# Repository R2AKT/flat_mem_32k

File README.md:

License addendum - https://github.com/R2AKT/flat_mem_32k/blob/main/Addendum.txt
# flat_mem_32k

32k flat (linear) memory board: 8k ROM + 8k EEPROM/RAM + 8k EEPROM/RAM + 8k RAM.
For Mega-80 (Mega-580) DIY 8-bit micro-computer - https://github.com/R2AKT/Mega-80.

ROM - 8k;
PROM - 8/16k;
RAM - 16/8k.

Status: not tested!

Плата плоской (линейной) памяти на 8к.
Для самодельной 8-битной микро-ЭВМ - https://github.com/R2AKT/Mega-80.

ПЗУ - 8кб;
ППЗУ - 8/16кб;
ОЗУ - 16/8кб.

Статус: не проверено!

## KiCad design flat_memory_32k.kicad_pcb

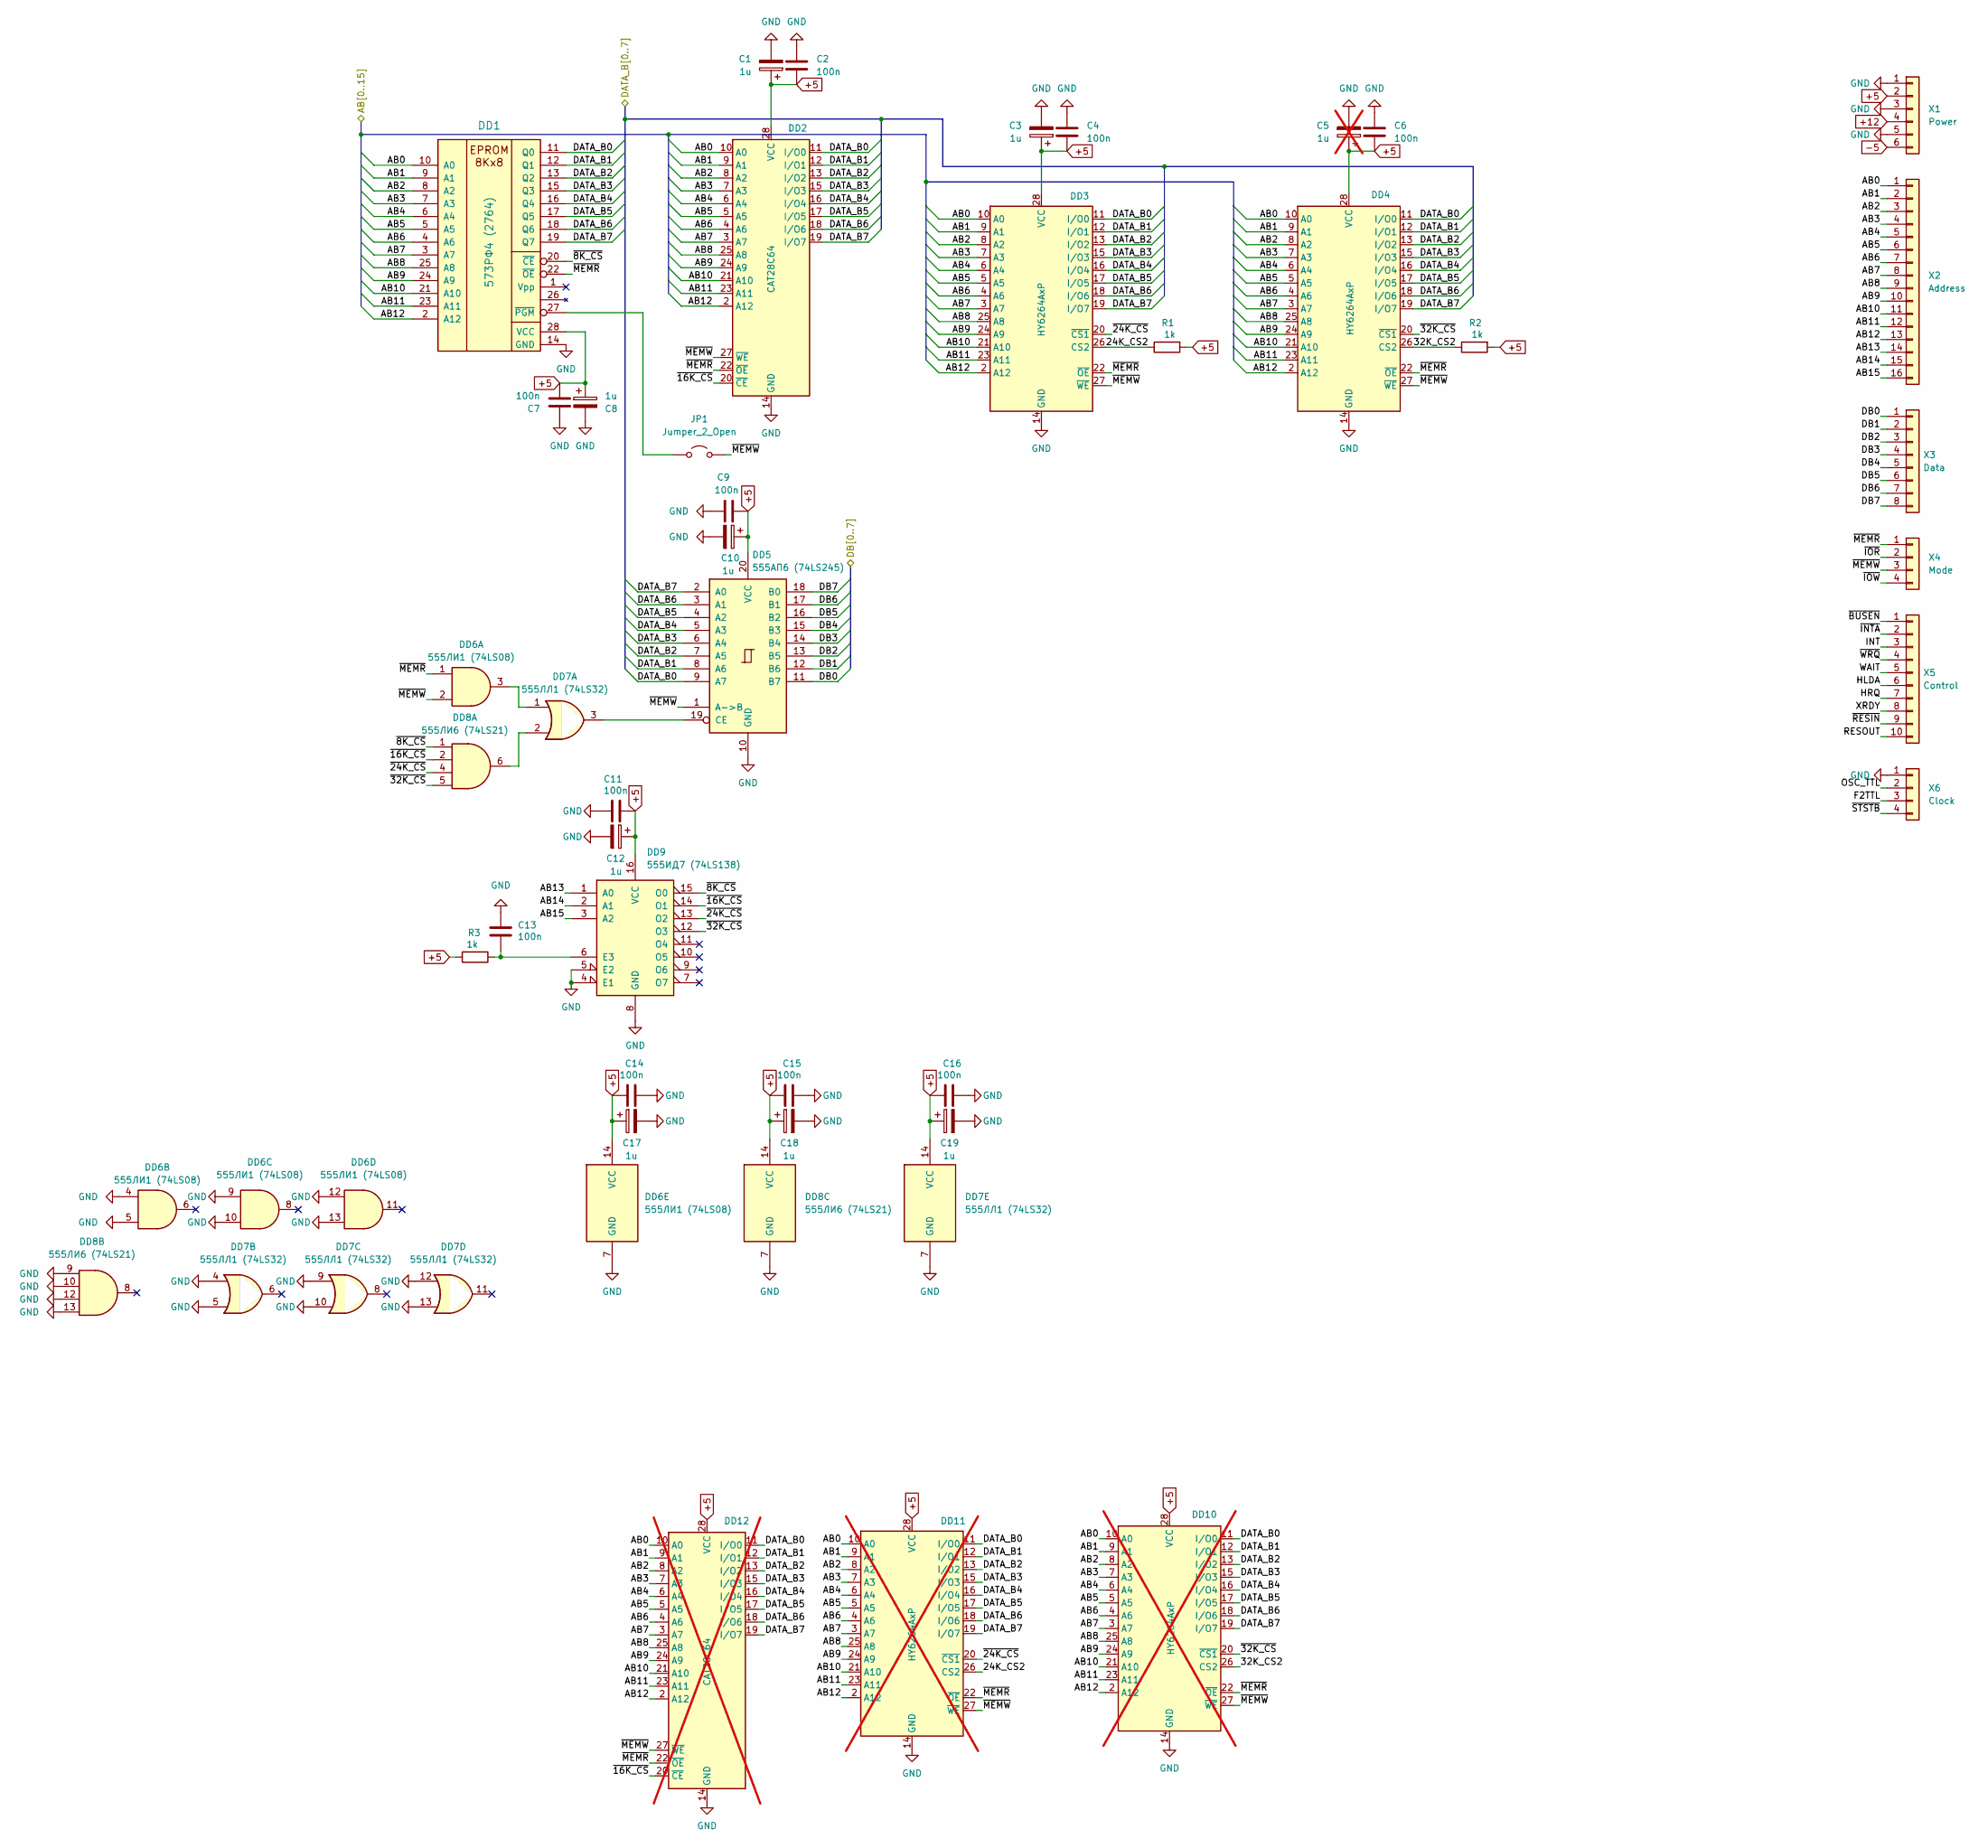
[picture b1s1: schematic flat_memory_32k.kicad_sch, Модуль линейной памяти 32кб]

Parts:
C1, C3, C8, C10, C12, C17, C18, C19: 1u; CP_EIA-3216-18_Kemet-A_Pad1.58x1.35mm_HandSolder
C2, C4, C6, C7, C9, C11, C13, C14, C15, C16: 100n; C_0805_2012Metric_Pad1.18x1.45mm_HandSolder
C5: 1u; CP_EIA-3216-18_Kemet-A_Pad1.58x1.35mm_HandSolder; not fitted
DD1: 573РФ4 (2764); DIP-28_W15.24mm_Socket_LongPads
DD2: CAT28C64; DIP-28_W15.24mm_Socket_LongPads
DD3, DD4: HY6264AxP; DIP-28_W15.24mm_Socket_LongPads
DD5: 555АП6 (74LS245); DIP-20_W7.62mm_Socket_LongPads
DD6: 555ЛИ1 (74LS08); DIP-14_W7.62mm_Socket_LongPads
DD7: 555ЛЛ1 (74LS32); DIP-14_W7.62mm_Socket_LongPads
DD8: 555ЛИ6 (74LS21); DIP-14_W7.62mm_Socket_LongPads
DD9: 555ИД7 (74LS138); DIP-16_W7.62mm_Socket_LongPads
DD10, DD11: HY6264AxP; DIP-28_W7.62mm_Socket_LongPads; not fitted
DD12: CAT28C64; DIP-28_W7.62mm_Socket_LongPads; not fitted
JP1: Jumper_2_Open; SolderJumper-2_P1.3mm_Open_RoundedPad1.0x1.5mm
R1, R2, R3: 1k; R_0805_2012Metric_Pad1.20x1.40mm_HandSolder
X1: Power; PinHeader_1x06_P2.54mm_Vertical
X2: Address; PinHeader_1x16_P2.54mm_Vertical
X3: Data; PinHeader_1x08_P2.54mm_Vertical
X4: Mode; PinHeader_1x04_P2.54mm_Vertical
X5: Control; PinHeader_1x10_P2.54mm_Vertical
X6: Clock; PinHeader_1x04_P2.54mm_Vertical

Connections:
+5: C1.1, C2.1, C3.1, C4.1, C5.1, C6.1, C7.1, C8.1, C9.1, C10.1, C11.1, C12.1, C14.1, C15.1, C16.1, C17.1, C18.1, C19.1, DD1.28 (VCC), DD2.28 (VCC), DD3.28 (VCC), DD4.28 (VCC), DD5.20 (VCC), DD6.14 (VCC), DD7.14 (VCC), DD8.14 (VCC), DD9.16 (VCC), DD10.28 (VCC), DD11.28 (VCC), DD12.28 (VCC), R1.2, R2.2, R3.2, X1.2
+12: X1.4
-5: X1.6
/24K_CS2: DD3.26 (CS2), DD11.26 (CS2), R1.1
/32K_CS2: DD4.26 (CS2), DD10.26 (CS2), R2.1
/AB0: DD1.10 (A0), DD2.10 (A0), DD3.10 (A0), DD4.10 (A0), DD10.10 (A0), DD11.10 (A0), DD12.10 (A0), X2.1
/AB1: DD1.9 (A1), DD2.9 (A1), DD3.9 (A1), DD4.9 (A1), DD10.9 (A1), DD11.9 (A1), DD12.9 (A1), X2.2
/AB2: DD1.8 (A2), DD2.8 (A2), DD3.8 (A2), DD4.8 (A2), DD10.8 (A2), DD11.8 (A2), DD12.8 (A2), X2.3
/AB3: DD1.7 (A3), DD2.7 (A3), DD3.7 (A3), DD4.7 (A3), DD10.7 (A3), DD11.7 (A3), DD12.7 (A3), X2.4
/AB4: DD1.6 (A4), DD2.6 (A4), DD3.6 (A4), DD4.6 (A4), DD10.6 (A4), DD11.6 (A4), DD12.6 (A4), X2.5
/AB5: DD1.5 (A5), DD2.5 (A5), DD3.5 (A5), DD4.5 (A5), DD10.5 (A5), DD11.5 (A5), DD12.5 (A5), X2.6
/AB6: DD1.4 (A6), DD2.4 (A6), DD3.4 (A6), DD4.4 (A6), DD10.4 (A6), DD11.4 (A6), DD12.4 (A6), X2.7
/AB7: DD1.3 (A7), DD2.3 (A7), DD3.3 (A7), DD4.3 (A7), DD10.3 (A7), DD11.3 (A7), DD12.3 (A7), X2.8
/AB8: DD1.25 (A8), DD2.25 (A8), DD3.25 (A8), DD4.25 (A8), DD10.25 (A8), DD11.25 (A8), DD12.25 (A8), X2.9
/AB9: DD1.24 (A9), DD2.24 (A9), DD3.24 (A9), DD4.24 (A9), DD10.24 (A9), DD11.24 (A9), DD12.24 (A9), X2.10
/AB10: DD1.21 (A10), DD2.21 (A10), DD3.21 (A10), DD4.21 (A10), DD10.21 (A10), DD11.21 (A10), DD12.21 (A10), X2.11
/AB11: DD1.23 (A11), DD2.23 (A11), DD3.23 (A11), DD4.23 (A11), DD10.23 (A11), DD11.23 (A11), DD12.23 (A11), X2.12
/AB12: DD1.2 (A12), DD2.2 (A12), DD3.2 (A12), DD4.2 (A12), DD10.2 (A12), DD11.2 (A12), DD12.2 (A12), X2.13
/AB13: DD9.1 (A0), X2.14
/AB14: DD9.2 (A1), X2.15
/AB15: DD9.3 (A2), X2.16
/DATA_B0: DD1.11 (Q0), DD2.11 (I/O0), DD3.11 (I/O0), DD4.11 (I/O0), DD5.9 (A7), DD10.11 (I/O0), DD11.11 (I/O0), DD12.11 (I/O0)
/DATA_B1: DD1.12 (Q1), DD2.12 (I/O1), DD3.12 (I/O1), DD4.12 (I/O1), DD5.8 (A6), DD10.12 (I/O1), DD11.12 (I/O1), DD12.12 (I/O1)
/DATA_B2: DD1.13 (Q2), DD2.13 (I/O2), DD3.13 (I/O2), DD4.13 (I/O2), DD5.7 (A5), DD10.13 (I/O2), DD11.13 (I/O2), DD12.13 (I/O2)
/DATA_B3: DD1.15 (Q3), DD2.15 (I/O3), DD3.15 (I/O3), DD4.15 (I/O3), DD5.6 (A4), DD10.15 (I/O3), DD11.15 (I/O3), DD12.15 (I/O3)
/DATA_B4: DD1.16 (Q4), DD2.16 (I/O4), DD3.16 (I/O4), DD4.16 (I/O4), DD5.5 (A3), DD10.16 (I/O4), DD11.16 (I/O4), DD12.16 (I/O4)
/DATA_B5: DD1.17 (Q5), DD2.17 (I/O5), DD3.17 (I/O5), DD4.17 (I/O5), DD5.4 (A2), DD10.17 (I/O5), DD11.17 (I/O5), DD12.17 (I/O5)
/DATA_B6: DD1.18 (Q6), DD2.18 (I/O6), DD3.18 (I/O6), DD4.18 (I/O6), DD5.3 (A1), DD10.18 (I/O6), DD11.18 (I/O6), DD12.18 (I/O6)
/DATA_B7: DD1.19 (Q7), DD2.19 (I/O7), DD3.19 (I/O7), DD4.19 (I/O7), DD5.2 (A0), DD10.19 (I/O7), DD11.19 (I/O7), DD12.19 (I/O7)
/DB0: DD5.11 (B7), X3.1
/DB1: DD5.12 (B6), X3.2
/DB2: DD5.13 (B5), X3.3
/DB3: DD5.14 (B4), X3.4
/DB4: DD5.15 (B3), X3.5
/DB5: DD5.16 (B2), X3.6
/DB6: DD5.17 (B1), X3.7
/DB7: DD5.18 (B0), X3.8
/HLDA: X5.6
/HRQ: X5.7
/INT: X5.3
/INTE: X5.4
/RESOUT: X5.10
/Single_BCLK: X6.3
/Single_OSC_TTL: X6.2
/WAIT: X5.5
/XRDY: X5.8
/~8K_CS: DD1.20 (~CE), DD8.1, DD9.15 (O0)
/~16K_CS: DD2.20 (~CE), DD8.2, DD9.14 (O1), DD12.20 (~CE)
/~24K_CS: DD3.20 (~CS1), DD8.4, DD9.13 (O2), DD11.20 (~CS1)
/~32K_CS: DD4.20 (~CS1), DD8.5, DD9.12 (O3), DD10.20 (~CS1)
/~BUSEN: X5.1
/~INTA: X5.2
/~IOR: X4.2
/~IOW: X4.4
/~MEMR: DD1.22 (~OE), DD2.22 (~OE), DD3.22 (~OE), DD4.22 (~OE), DD6.1, DD10.22 (~OE), DD11.22 (~OE), DD12.22 (~OE), X4.1
/~MEMW: DD2.27 (~WE), DD3.27 (~WE), DD4.27 (~WE), DD5.1 (A->B), DD6.2, DD10.27 (~WE), DD11.27 (~WE), DD12.27 (~WE), JP1.2 (B), X4.3
/~RESIN: X5.9
/~STSTB: X6.4
GND: C1.2, C2.2, C3.2, C4.2, C5.2, C6.2, C7.2, C8.2, C9.2, C10.2, C11.2, C12.2, C13.1, C14.2, C15.2, C16.2, C17.2, C18.2, C19.2, DD1.14 (GND), DD2.14 (GND), DD3.14 (GND), DD4.14 (GND), DD5.10 (GND), DD6.4, DD6.5, DD6.7 (GND), DD6.9, DD6.10, DD6.12, DD6.13, DD7.4, DD7.5, DD7.7 (GND), DD7.9, DD7.10, DD7.12, DD7.13, DD8.7 (GND), DD8.9, DD8.10, DD8.12, DD8.13, DD9.4 (E1), DD9.5 (E2), DD9.8 (GND), DD10.14 (GND), DD11.14 (GND), DD12.14 (GND), X1.1, X1.3, X1.5, X6.1
unnamed: DD1.27 (~PGM), JP1.1 (A)
unnamed: DD5.19 (CE), DD7.3
unnamed: DD6.3, DD7.1
unnamed: DD7.2, DD8.6
unnamed: C13.2, DD9.6 (E3), R3.1

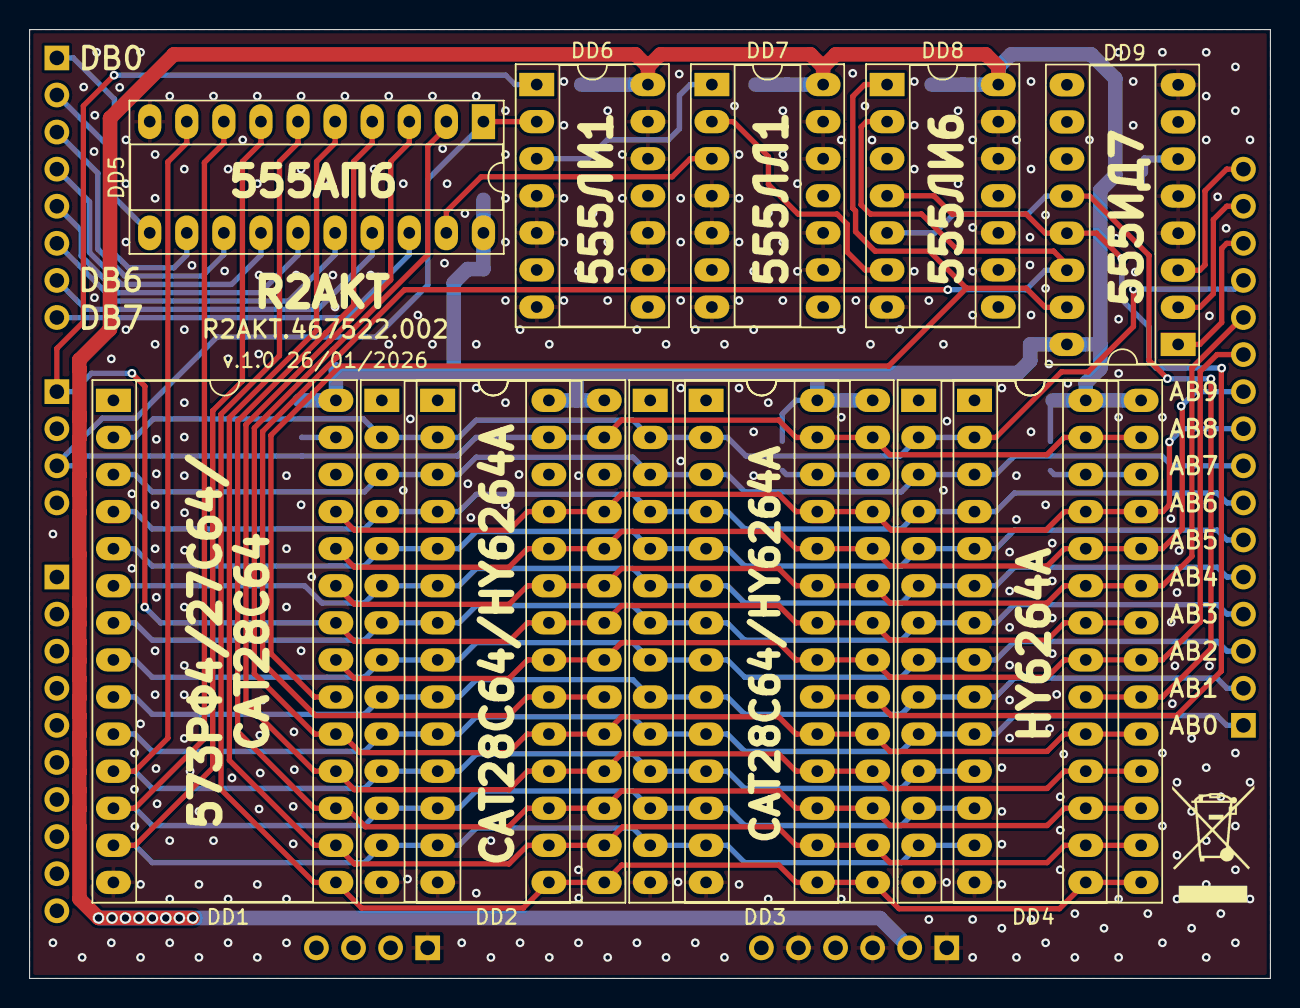
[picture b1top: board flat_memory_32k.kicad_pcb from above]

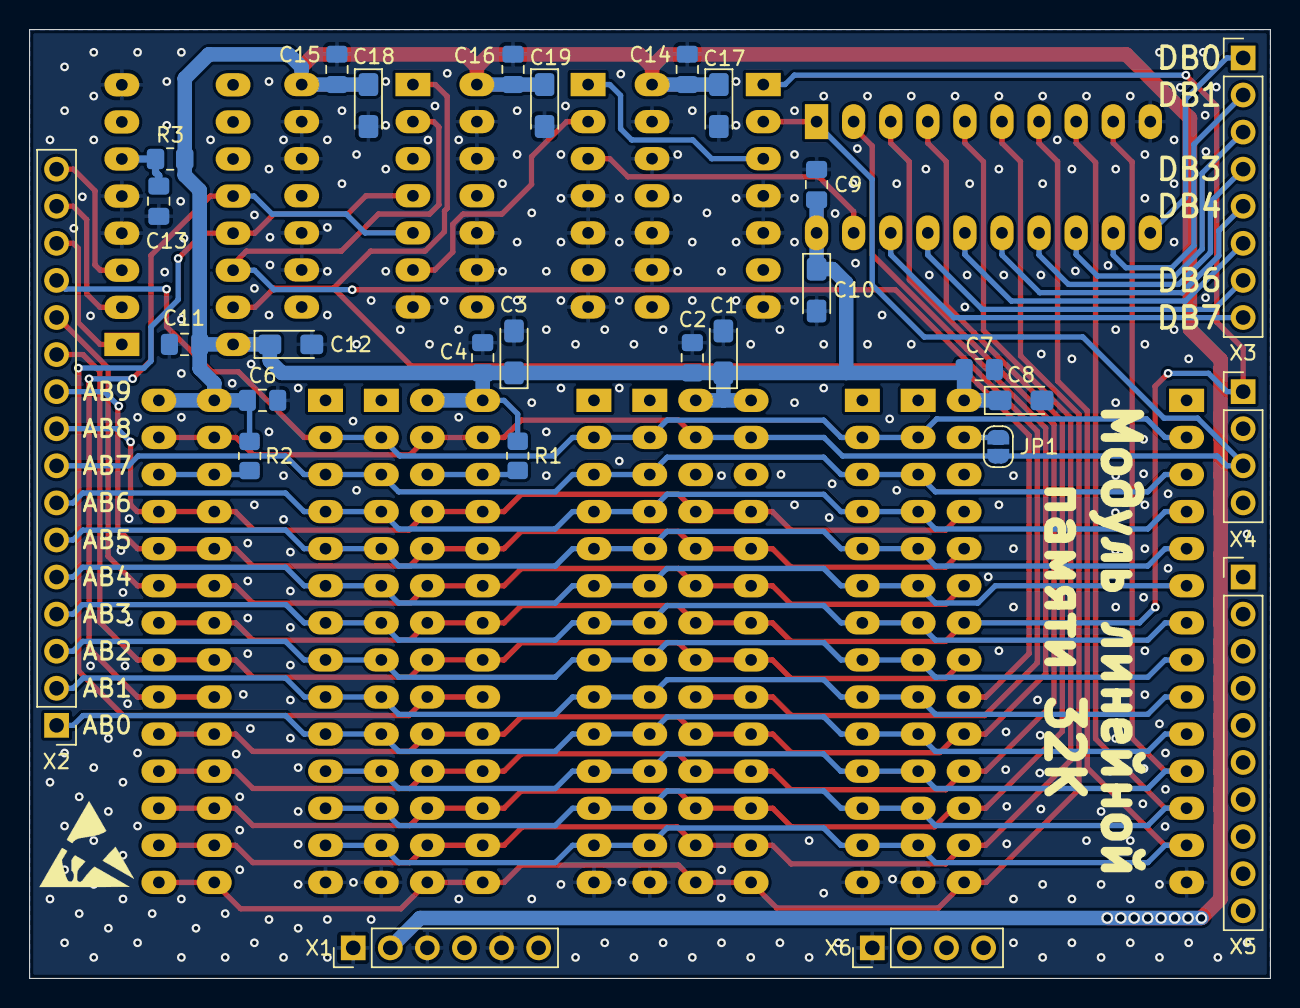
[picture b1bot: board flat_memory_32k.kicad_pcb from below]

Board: 2 copper layers, 85.0 x 65.0 mm, 40 parts (28 on the bottom side), 47 nets.

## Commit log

2026-06-17 Fix silk

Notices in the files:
README.md:
License: MIT
